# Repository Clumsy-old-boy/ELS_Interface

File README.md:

<!-- PROJECT SHIELDS -->
[![License][license-shield]][license-url][![Platform][platform-shield]][platform-url][![Toolchain][toolchain-shield]][toolchain-url][![Verified][verified-shield]][verified-url]

<!-- PROJECT LOGO -->
<br />
<div align="center">
  <h3 align="center">ELS_Interface — NUCLEO-G474RE Shield</h3>

  <p align="center">
    Carrier board for the STM32G474RE (NUCLEO-G474RE) that puts on a single
    70 × 70 mm PCB the field interface of an electronic machine controller:
    12 V → 5 V buck supply, serial display connector, 2×10 IDC field I/O with
    level shifting and opto-isolated outputs, I²C EEPROM and two debug LEDs.
    <br />
    <a href="#documentation"><strong>See the Documentation »</strong></a>
    <br />
    <br />
    <a href="#about-the-project">About</a>
    &middot;
    <a href="#getting-started">Getting Started</a>
    &middot;
    <a href="#verification">Verification</a>
    &middot;
    <a href="#production-files">Production Files</a>
  </p>
</div>

<!-- TABLE OF CONTENTS -->
<details>
  <summary>Table of Contents</summary>
  <ol>
    <li>
      <a href="#about-the-project">About The Project</a>
      <ul>
        <li><a href="#main-features">Main Features</a></li>
        <li><a href="#built-with">Built With</a></li>
      </ul>
    </li>
    <li>
      <a href="#getting-started">Getting Started</a>
      <ul>
        <li><a href="#prerequisites">Prerequisites</a></li>
        <li><a href="#installation">Installation</a></li>
      </ul>
    </li>
    <li><a href="#documentation">Documentation</a></li>
    <li><a href="#usage">Usage</a></li>
    <li><a href="#verification">Verification</a></li>
    <li><a href="#production-files">Production Files</a></li>
    <li><a href="#repository-structure">Repository Structure</a></li>
    <li><a href="#known-issues--limitations">Known Issues & Limitations</a></li>
    <li><a href="#contributing">Contributing</a></li>
    <li><a href="#license">License</a></li>
    <li><a href="#acknowledgments">Acknowledgments</a></li>
  </ol>
</details>

<!-- ABOUT THE PROJECT -->
## About The Project

**ELS_Interface** is a KiCad shield for the **NUCLEO-G474RE**
(STMicroelectronics **STM32G474RET6**, LQFP64). It plugs onto the two morpho
headers of the Nucleo board and carries the machine-side interface of an
electronic lead-screw (ELS) controller.

The board is a **2-layer design**, 70 × 70 mm, 1 oz copper, routed and
**DRC-clean** (0 active violations, 0 unconnected nets), with a fully filled
copper pour on both sides.

The 12 V field supply enters on a screw terminal, is protected and stepped
down to 5 V by a **TPS5430** buck converter; the 5 V rail of the shield can be
fed either from that buck or from the Nucleo USB supply through a **diode-OR**
(D4 / D5), so the board can be brought up on the bench without the 12 V
connected. The Nucleo itself is fed on the **E5V** pin (CN7-6) directly from
the buck, which keeps that pin inside the 4.75–5.25 V range specified by ST
(UM2505).

> [!WARNING]
> Hobbyist / educational project, **not certified**. The board works on 12 V
> and switches field signals through optocouplers, but no functional-safety
> claim is made: verify every interface against your machine before use.
> <br>
> This project was developed with the support of artificial intelligence
> tools — see [Verification](#verification).

### Main Features

| Item | Value |
|---|---|
| Board size | **70 × 70 mm**, 2 layers, 1 oz copper |
| MCU board | NUCLEO-G474RE (STM32G474RET6) via J1 (CN7) + J2 (CN10), 2×19, 2.54 mm |
| Supply input | **12 V DC** on J3 (2-pole screw terminal), protected by F1 polyfuse + TVS D1 |
| 5 V generation | **TPS5430** buck, 5 V / up to 3 A, L1 22 µH, C5 220 µF |
| Supply selection | **diode-OR D4/D5** (12 V rail vs. USB) on the shield 5 V rail |
| MCU supply | E5V (CN7-6), 5.00 V direct, jumper **JP5 = 5-6** on the Nucleo |
| Display | **J7** — 8-pin 2.00 mm (DWIN DMG10600C101), 12 V + TTL UART |
| Field I/O | **J5** — IDC 2×10, level-shifted by **TXB0104** |
| Isolated outputs | **3 × PC817** optocouplers → **J8** (5-pole screw terminal) |
| Memory | **M24M01E** 1 Mbit I²C EEPROM (IC1) |
| Debug LEDs | LED1 green on **PA0**, LED2 red on **PA1**, 0402 resistors |
| Assembly | **56 components**, JLCPCB-ready (BOM + CPL + LCSC codes) |

### Built With

* [![KiCad][kicad-shield]][kicad-url]
* [![STMicroelectronics][st-shield]][st-url]
* [Electra 6.x](https://www.layouteditor.com/) — autorouter used for the initial PCB routing

<p align="right">(<a href="#readme-top">back to top</a>)</p>

<!-- GETTING STARTED -->
## Getting Started

### Prerequisites

* **KiCad 10** (developed and verified with **10.0.6**).
* No external libraries are needed: symbols, footprints and 3D models are
  stored inside `library/` and referenced with `${KIPRJMOD}`.

### Installation

1. Clone the repository:
   ```sh
   git clone https://github.com/Clumsy-old-boy/ELS_Interface.git
   ```
2. Open `ELS_Interface.kicad_pro` with KiCad 10.
3. Check that the library tables are loaded: *Preferences → Manage Symbol
   Libraries* and *Manage Footprint Libraries* must show `ELS_Custom`,
   `User_Library`, `User_Footprints` and the `PCM_*_AKL` entries, all with
   `${KIPRJMOD}` paths.

<p align="right">(<a href="#readme-top">back to top</a>)</p>

<!-- DOCUMENTATION -->
## Documentation

| Document | File | Description |
|---|---|---|
| Usage | [`docs/USAGE.md`](docs/USAGE.md) | Supply, connectors, LEDs, Nucleo jumper JP5 |
| Configuration | [`docs/CONFIGURATION.md`](docs/CONFIGURATION.md) | Pinout, connected components, logic levels, connector map |
| Test procedure | [`docs/TEST_PROCEDURE.md`](docs/TEST_PROCEDURE.md) | Power-up, LED, opto, display and IDC tests |
| User guide (PDF) | [`docs/USAGE.pdf`](docs/USAGE.pdf) | Printable user guide, 8 pages |
| Configuration (PDF) | [`docs/CONFIGURATION.pdf`](docs/CONFIGURATION.pdf) | Printable hardware configuration, 8 pages |
| Test procedure (PDF) | [`docs/TEST_PROCEDURE.pdf`](docs/TEST_PROCEDURE.pdf) | Printable bench checklist, 11 pages |
| Schematic | [`docs/ELS_Interface_schematics.pdf`](docs/ELS_Interface_schematics.pdf) | Full schematic, single A4 sheet, with title block and revision |
| PCB layout | [`docs/pcb.pdf`](docs/pcb.pdf) | Top view with all **55** reference designators and bottom view with the two morpho sockets (J1/J2) — 2 pages |
| Interactive BOM | [`docs/ELS_Interface_ibom.html`](docs/ELS_Interface_ibom.html) | Interactive assembly drawing (iBOM), generated with InteractiveHtmlBom |
| 3D render | [`docs/ELS_Interface_board.png`](docs/ELS_Interface_board.png) | Top 3D view of the assembled board, transparent background |

<p align="right">(<a href="#readme-top">back to top</a>)</p>

<!-- USAGE -->
## Usage

Quick start:

1. Set **JP5 on the Nucleo to pins 5-6 (`E5V`)** if the board supplies the
   Nucleo from 12 V.
2. Connect **12 V** to `J3` (pin 1 = +12 V, pin 2 = GND).
3. The **LED1 (green)** and **LED2 (red)** are driven by PA0 and PA1 of the
   firmware; they are debug indicators, not power indicators.
4. The shield 5 V rail is taken from the buck when 12 V is present, or from
   USB (through D5) when the board is used on the bench.

Full details: [`docs/USAGE.md`](docs/USAGE.md).

<p align="right">(<a href="#readme-top">back to top</a>)</p>

<!-- VERIFICATION -->
## Verification

The schematic and the PCB were verified with the **`kicad-mcp-pro`** MCP
server (KiCad 10.0.6) and with **`kicad-cli`**. The checks below were run on
the exact files contained in this repository.

| Check | Tool | Result |
|---|---|---|
| **ERC** — Electrical Rules Check | `kicad-mcp-pro` / `kicad-cli` | **0 violations** |
| **DRC** — Design Rules Check incl. custom JLCPCB rules | `kicad-mcp-pro` / `kicad-cli` | **0 active violations**, **0 unconnected items** |
| **Netlist** export | `kicad-cli sch export netlist` | completed, **56 components** |
| **Schematic ↔ PCB parity** | `kicad-mcp-pro` (`validate_footprints_vs_schematic`) | **56 refs = 56 refs**, 0 missing in both directions |
| **Connectivity** | `kicad-mcp-pro` (`pcb_get_ratsnest`) | **0 unconnected nets** |
| **DFM (JLCPCB)** | measurement on the `.kicad_pcb` | 2 layers · min track 0.25 mm · via 0.40/0.80 mm · min PTH 0.30 mm · 0 silk-to-pad violations |

> [!NOTE]
> Two DRC items are **excluded in the project** on purpose and are therefore
> not counted as active violations:
> `U1` *footprint type mismatch* (the SO-PowerPAD footprint of the TPS5430 has
> thermal vias, which the checker reports as an SMD/through-hole mismatch) and
> `F1` *footprint differs from the library copy* (a locally adjusted polyfuse
> footprint, already reflected in the Gerber files).

<p align="right">(<a href="#readme-top">back to top</a>)</p>

<!-- PRODUCTION -->
## Production Files

Everything needed to order the PCB and the SMT assembly at **JLCPCB**:

| File | Content |
|---|---|
| [`production/GERBER-ELS_Interface.zip`](jlcpcb/production_files/GERBER-ELS_Interface.zip) | Gerber (9 layers) + PTH / NPTH drill files |
| [`production/BOM-ELS_Interface.csv`](jlcpcb/production_files/BOM-ELS_Interface.csv) | Bill of materials with **LCSC part numbers** (50 components) |
| [`production/CPL-ELS_Interface.csv`](jlcpcb/production_files/CPL-ELS_Interface.csv) | Component placement (designator, X, Y, rotation, layer) |

Manufacturing rules matching JLCPCB 2-layer / 1 oz capability are in
[`ELS_Interface.kicad_dru`](ELS_Interface.kicad_dru).

> [!IMPORTANT]
> The through-hole connectors (J1, J2, J3, J5, J7, J8) are **excluded from
> the BOM and CPL** on purpose: they are not assembled by JLCPCB and must be
> soldered by hand.

<p align="right">(<a href="#readme-top">back to top</a>)</p>

<!-- REPOSITORY STRUCTURE -->
## Repository Structure

```
ELS_Interface/
├── ELS_Interface.kicad_pro      KiCad project
├── ELS_Interface.kicad_sch      Schematic
├── ELS_Interface.kicad_pcb      PCB, routed and DRC-clean
├── ELS_Interface.kicad_dru      Custom DRC rules for JLCPCB (2 layers, 1 oz)
├── fp-lib-table                 Footprint library table (${KIPRJMOD})
├── sym-lib-table                Symbol library table (${KIPRJMOD})
├── library/                     Project libraries and 3D models
│   ├── ELS_Custom.kicad_sym     Project-specific symbols
│   ├── ELS_Custom.pretty/       Project-specific footprints
│   ├── User_Library.kicad_sym   Power symbols (E5V, V_5V_SHIELD)
│   ├── User_Footprints.pretty/  Extra footprints (SOIC-8)
│   ├── *_AKL.kicad_sym          Alternate KiCad Library (vendored)
│   ├── *_AKL.pretty/            Alternate KiCad Library footprints (vendored)
│   └── 3d/                      STEP models used by the board
├── docs/                        PDF schematic, PCB view, iBOM and guides
└── jlcpcb/production_files/     Gerber ZIP, BOM, CPL — ready for JLCPCB
```

<p align="right">(<a href="#readme-top">back to top</a>)</p>

<!-- KNOWN ISSUES -->
### Known Issues & Limitations

- **Nucleo jumper JP5 must be set correctly**: `5-6` (E5V) when the board
  supplies the Nucleo, `1-2` (STLK) when the Nucleo is powered from USB.
- **Through-hole connectors are not assembled** by the SMT service; the
  40-pin morpho headers (J1/J2) and J3/J5/J7/J8 must be soldered by hand.
- **I²C3 pin mapping**: the `.ioc` enables I2C3 with custom timing but does not
  assign SCL/SDA; on the board the EEPROM is wired to **PC8/PC11** — confirm
  the mapping in CubeMX before generating the firmware.
- The **firmware is not included** in this repository: it lives in a separate
  STM32CubeMX/Keil project.
- The routing scripts used during development (Electra `.do` files and the
  Specctra `.dsn`) are not distributed with the repository.

<p align="right">(<a href="#readme-top">back to top</a>)</p>

<!-- CONTRIBUTING -->
## Contributing

1. Fork the Project
2. Create your Feature Branch (`git checkout -b feature/NewFeature`)
3. Commit your Changes (`git commit -m 'Add NewFeature'`)
4. Push to the Branch (`git push origin feature/NewFeature`)
5. Open a Pull Request

<p align="right">(<a href="#readme-top">back to top</a>)</p>

<!-- LICENSE -->
## License

Distributed under the **MIT** license. See [`LICENSE`](LICENSE) for the full text.

<p align="right">(<a href="#readme-top">back to top</a>)</p>

<!-- ACKNOWLEDGMENTS -->
## Acknowledgments

* [STMicroelectronics — STM32G4 Series](https://www.st.com/en/microcontrollers-microprocessors/stm32g4-series.html)
* [NUCLEO-G474RE user manual (UM2505)](https://www.st.com/resource/en/user_manual/um2505-stm32g4-nucleo64-boards-mb1367-stmicroelectronics.pdf)
* [JLCPCB PCB capabilities](https://jlcpcb.com/capabilities/pcb-capabilities)
* [kicad-druid — JLCPCB design rules for KiCad](https://github.com/Cimos/kicad-druid)
* [Best-README-Template](https://github.com/othneildrew/Best-README-Template) — structure of this README
* This project was developed with the support of artificial intelligence tools.

<p align="right">(<a href="#readme-top">back to top</a>)</p>

<!-- MARKDOWN LINKS & IMAGES -->
[license-shield]: https://img.shields.io/badge/license-MIT-yellow.svg?style=for-the-badge
[license-url]: LICENSE
[platform-shield]: https://img.shields.io/badge/MCU-STM32G474RE-03234B?style=for-the-badge
[platform-url]: https://www.st.com/en/microcontrollers-microprocessors/stm32g474re.html
[toolchain-shield]: https://img.shields.io/badge/toolchain-KiCad%2010-1C6BB0?style=for-the-badge
[toolchain-url]: https://www.kicad.org/
[verified-shield]: https://img.shields.io/badge/ERC%200%20%7C%20DRC%200-passing-brightgreen?style=for-the-badge
[verified-url]: #verification
[kicad-shield]: https://img.shields.io/badge/KiCad-10.0.6-1C6BB0?style=for-the-badge
[kicad-url]: https://www.kicad.org/
[st-shield]: https://img.shields.io/badge/STMicroelectronics-STM32G4-03234B?style=for-the-badge
[st-url]: https://www.st.com/en/microcontrollers-microprocessors/stm32g4-series.html

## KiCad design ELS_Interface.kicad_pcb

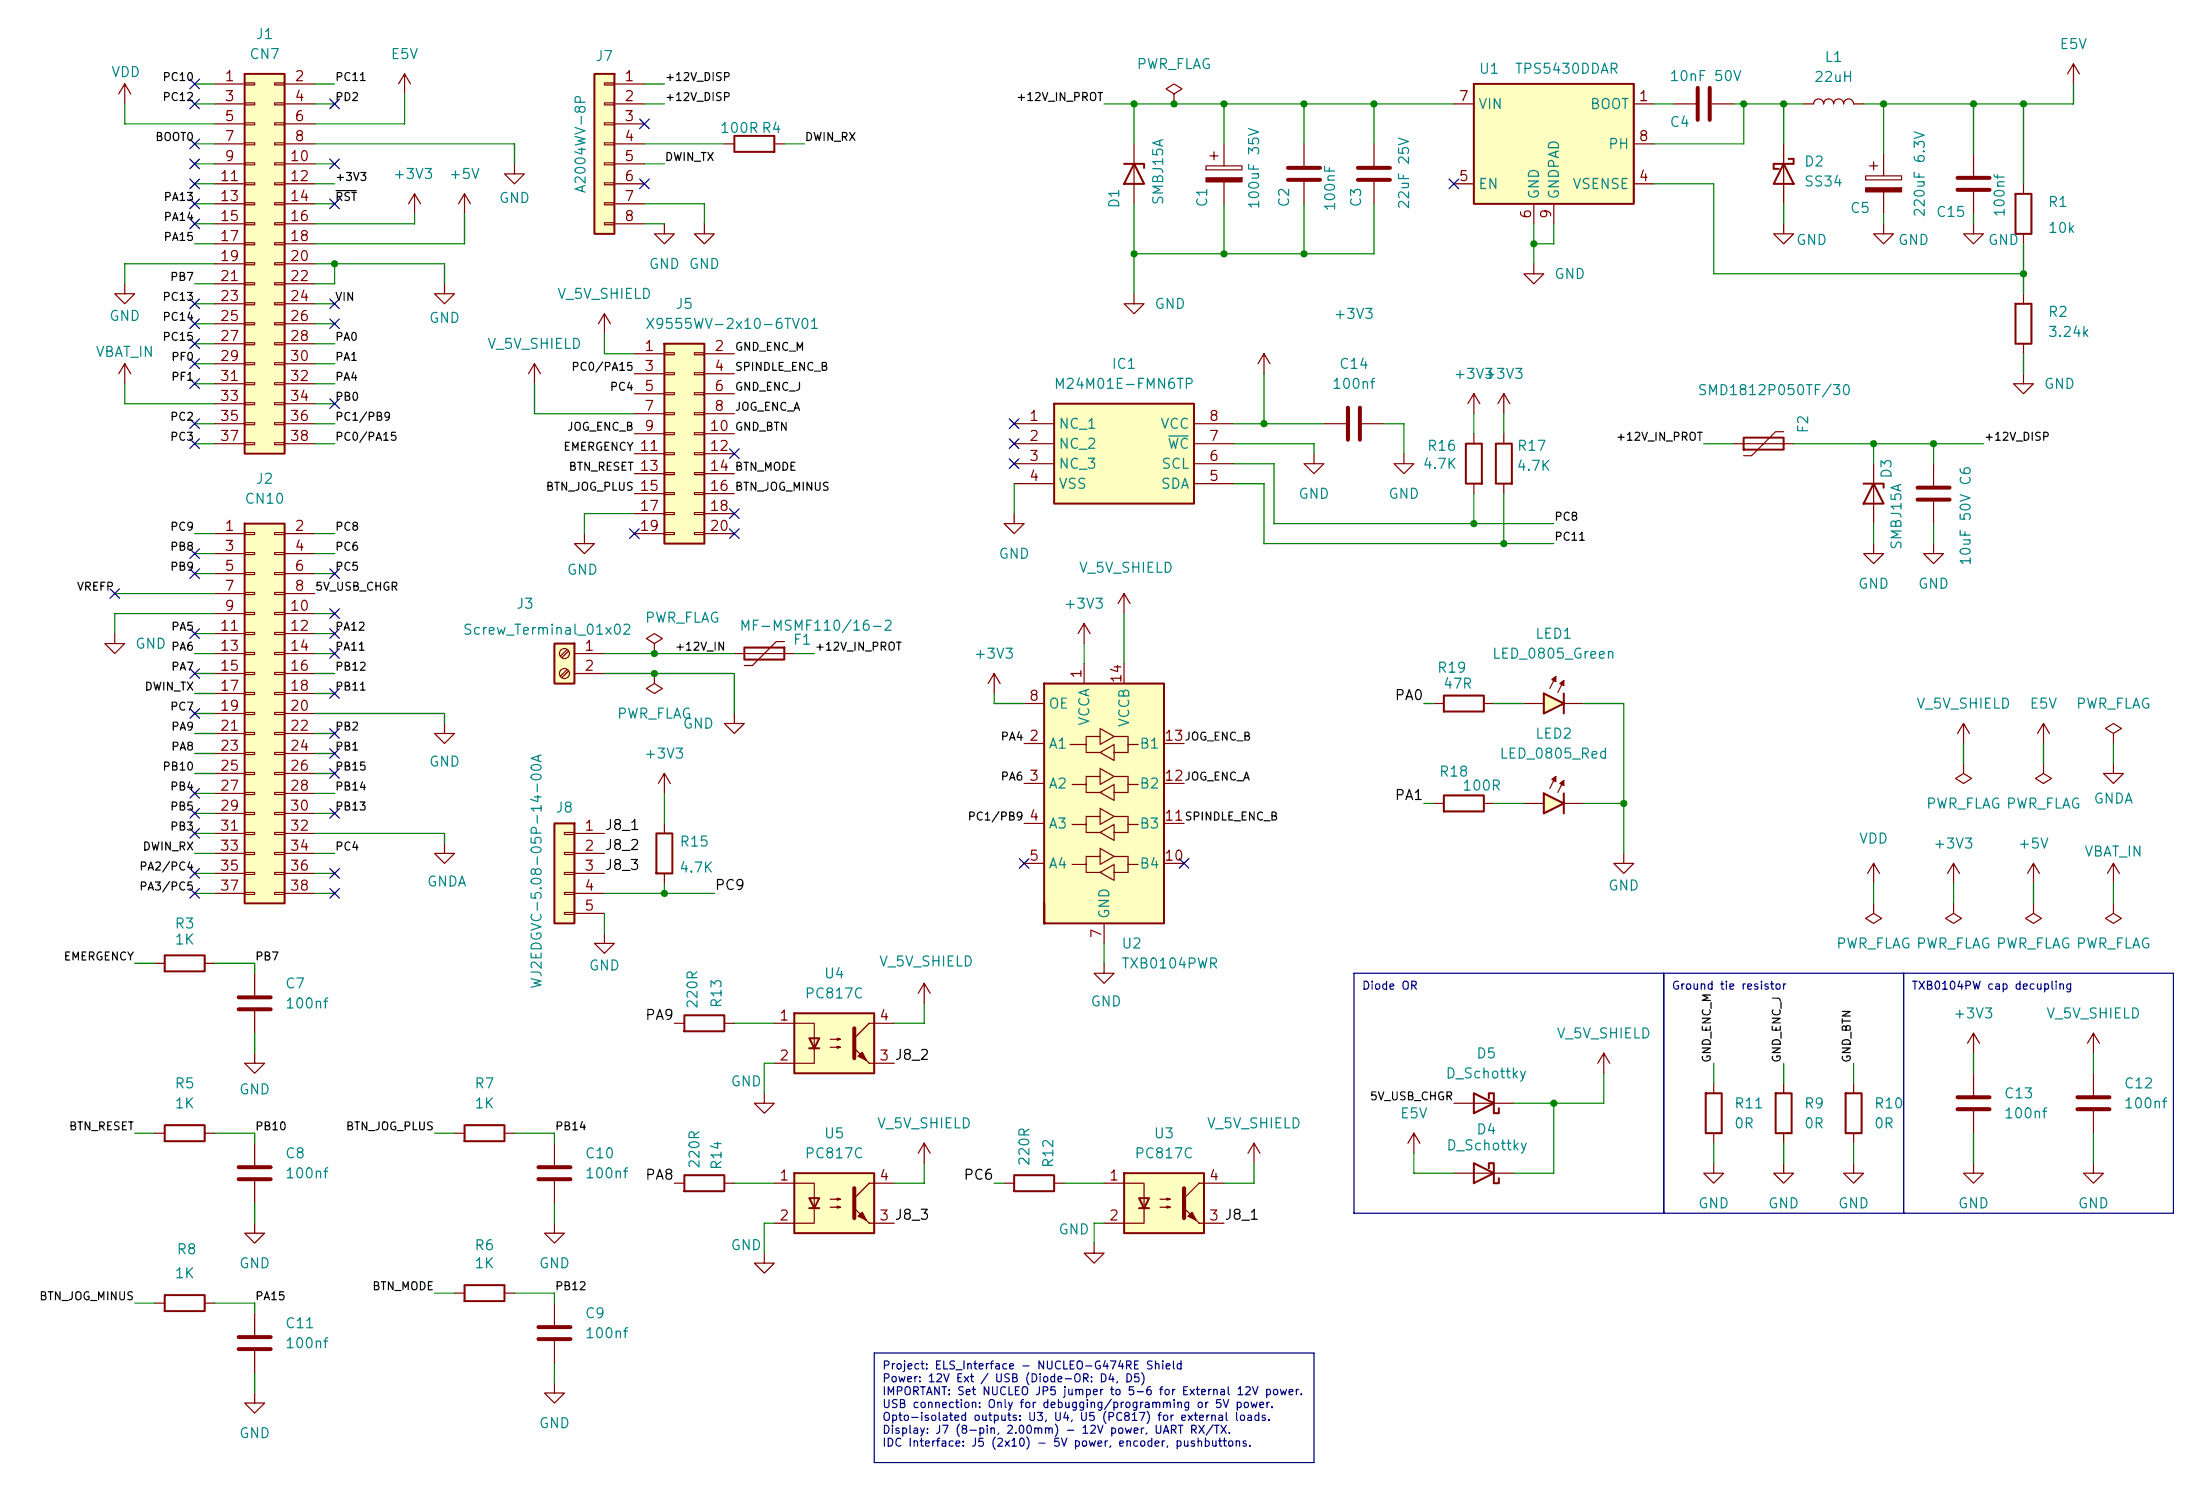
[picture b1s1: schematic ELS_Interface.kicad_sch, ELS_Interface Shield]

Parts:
C1: 100uF 35V; CP_Elec_6.3x7.7; MPN MA35V100M6X8; LCSC C46550467
C2: 100nF; C_0603_1608Metric; MPN CC0603KRX7R9BB104; LCSC C14663
C3: 22uF 25V; C_1210_3225Metric; MPN TCC1210X7R226K250MT; LCSC C49118556
C4: 10nF 50V; C_0805_2012Metric; MPN 08055C103KAT2A; LCSC C128911
C5: 220uF 6.3V; CP_EIA-3528-21_Kemet-B; MPN 6TPE220MAZB; LCSC C79111
C6: 10uF 50V; C_1206_3216Metric; MPN CL31A106KBHNNNE; LCSC C13585
C7, C8, C9, C10, C11, C12, C13, C14, C15: 100nf; C_0603_1608Metric; MPN CC0603KRX7R9BB104; LCSC C14663
D1, D3: SMBJ15A; D_SMB; MPN SMBJ15A; LCSC C188412
D2: SS34; D_SMB; MPN SS34; LCSC C908684
D4, D5: D_Schottky; D_SOD-123; LCSC C8598
F1: MF-MSMF110/16-2; Fuse_1812_4532Metric_JLCPCB; MPN MF-MSMF110/16-2; LCSC C210834
F2: SMD1812P050TF/30; Fuse_1812_4532Metric_JLCPCB; MPN SMD1812P050TF/30; LCSC C12559
IC1: M24M01E-FMN6TP; SOIC127P600X175-8N; Manufacturer_Part_Number M24M01E-FMN6TP; Mouser Part Number 511-M24M01E-FMN6TP
J1: CN7; PinSocket_2x19_P2.54mm_Vertical; MPN XDM254-2-19-Z-8.5-G0; LCSC C19268731
J2: CN10; PinSocket_2x19_P2.54mm_Vertical; MPN XDM254-2-19-Z-8.5-G0; LCSC C19268731
J3: Screw_Terminal_01x02; TerminalBlock_Phoenix_PT-1,5-2-3.5-H_1x02_P3.50mm_Horizontal; MPN DB125-3.5-2P-GN-S; LCSC C466970
J5: X9555WV-2x10-6TV01; IDC-Header_2x10_P2.54mm_Vertical; MPN X9555WV-2x10-6TV01; LCSC C2884550
J7: A2004WV-8P; CONN-TH_CNJMA2004WV-8P; MPN A2004WV-8P; LCSC C225246
J8: WJ2EDGVC-5.08-05P-14-00A; MPN WJ2EDGVC-5.08-05P-14-00A; LCSC C8423
L1: 22uH; L_Bourns-SRN8040_8x8.15mm; MPN FNR8065S220MT; LCSC C168163
LED1: LED_0805_Green; LED_0805_2012Metric; LCSC C2297
LED2: LED_0805_Red; LED_0805_2012Metric; LCSC C84256
R1: 10k; R_0402_1005Metric_Fixed; MPN 0402WGF1002TCE; LCSC C25744
R2: 3.24k; R_0402_1005Metric_Fixed; MPN CRCW04023K24FKED; LCSC C3972407
R3, R5, R6, R7, R8: 1K; R_0402_1005Metric_Fixed; MPN 0402WGF1001TCE; LCSC C11702
R4, R18: 100R; R_0402_1005Metric_Fixed; MPN 0402WGF1000TCE; LCSC C25076
R9, R10, R11: 0R; R_0603_1608Metric; MPN 0603WAF0000T5E; LCSC C21189
R12, R13, R14: 220R; R_0402_1005Metric_Fixed; MPN 0402WGF2200TCE; LCSC C25091
R15, R16, R17: 4.7K; R_0402_1005Metric_Fixed; MPN 0402WGF4701TCE; LCSC C25900
R19: 47R; R_0402_1005Metric_Fixed; MPN 0402WGF1000TCE; LCSC C25118
U1: TPS5430DDAR; TI_SO-PowerPAD-8_ThermalVias_JLCPCB; MPN TPS5430DDAR; LCSC C9864
U2: TXB0104PWR; TSSOP-14_4.4x5mm_P0.65mm; MPN TXB0104PWR; LCSC C60708
U3, U4, U5: PC817C; OPTO-SMD-4_L4.6-W6.5-P2.54-LS10.3-TL; MPN PC817C; LCSC C3025164

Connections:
+3V3: C13.1, C14.1, IC1.8 (VCC), J1.12, J1.16, R15.2, R16.2, R17.2, U2.1 (VCCA), U2.8 (OE)
+5V: J1.18
/5V_USB_CHGR: D5.2 (A), J2.8
/+12V_DISP: C6.1, D3.1 (K), F2.2, J7.1, J7.2
/+12V_IN: F1.2, J3.1
/+12V_IN_PROT: C1.1, C2.1, C3.1, D1.1 (K), F1.1, F2.1, U1.7 (VIN)
/BOOT0: J1.7
/BTN_JOG_MINUS: J5.16, R8.1
/BTN_JOG_PLUS: J5.15, R7.1
/BTN_MODE: J5.14, R6.1
/BTN_RESET: J5.13, R5.1
/DWIN_RX: J2.33, R4.1
/DWIN_TX: J2.17, J7.5
/EMERGENCY: J5.11, R3.1
/GND_BTN: J5.10, R10.1
/GND_ENC_J: J5.6, R9.1
/GND_ENC_M: J5.2, R11.1
/J8_1: J8.1, U3.3
/J8_2: J8.2, U4.3
/J8_3: J8.3, U5.3
/JOG_ENC_A: J5.8, U2.12 (B2)
/JOG_ENC_B: J5.9, U2.13 (B1)
/PA0: J1.28, R19.1
/PA1: J1.30, R18.1
/PA2/PC4: J2.35
/PA3/PC5: J2.37
/PA4: J1.32, U2.2 (A1)
/PA5: J2.11
/PA6: J2.13, U2.3 (A2)
/PA7: J2.15
/PA8: J2.23, R14.1
/PA9: J2.21, R13.1
/PA11: J2.14
/PA12: J2.12
/PA13: J1.13
/PA14: J1.15
/PA15: C11.1, J1.17, R8.2
/PB0: J1.34
/PB1: J2.24
/PB2: J2.22
/PB3: J2.31
/PB4: J2.27
/PB5: J2.29
/PB7: C7.1, J1.21, R3.2
/PB8: J2.3
/PB9: J2.5
/PB10: C8.1, J2.25, R5.2
/PB11: J2.18
/PB12: C9.1, J2.16, R6.2
/PB13: J2.30
/PB14: C10.1, J2.28, R7.2
/PB15: J2.26
/PC0/PA15: J1.38, J5.3
/PC1/PB9: J1.36, U2.4 (A3)
/PC2: J1.35
/PC3: J1.37
/PC4: J2.34, J5.5
/PC5: J2.6
/PC6: J2.4, R12.1
/PC7: J2.19
/PC8: IC1.6 (SCL), J2.2, R16.1
/PC9: J2.1, J8.4, R15.1
/PC10: J1.1
/PC11: IC1.5 (SDA), J1.2, R17.1
/PC12: J1.3
/PC13: J1.23
/PC14: J1.25
/PC15: J1.27
/PD2: J1.4
/PF0: J1.29
/PF1: J1.31
/SPINDLE_ENC_B: J5.4, U2.11 (B3)
/VIN: J1.24
/VREFP: J2.7
/~RST: J1.14
E5V: C5.1, C15.1, D4.2 (A), J1.6, L1.2, R1.1
GND: C1.2, C2.2, C3.2, C5.2, C6.2, C7.2, C8.2, C9.2, C10.2, C11.2, C12.2, C13.2, C14.2, C15.2, D1.2 (A), D2.2 (A), D3.2 (A), IC1.4 (VSS), IC1.7 (~WC), J1.8, J1.19, J1.20, J1.22, J2.9, J2.20, J3.2, J5.17, J7.7, J7.8, J8.5, LED1.1 (K), LED2.1 (K), R2.2, R9.2, R10.2, R11.2, U1.6 (GND), U1.9 (GNDPAD), U2.7 (GND), U3.2, U4.2, U5.2
GNDA: J2.32
unnamed: C4.2, D2.1 (K), L1.1, U1.8 (PH)
unnamed: J7.4, R4.2
unnamed: LED1.2 (A), R19.2
unnamed: LED2.2 (A), R18.2
unnamed: R12.2, U3.1
unnamed: R13.2, U4.1
unnamed: R14.2, U5.1
unnamed: C4.1, U1.1 (BOOT)
unnamed: R1.2, R2.1, U1.4 (VSENSE)
VBAT_IN: J1.33
VDD: J1.5
V_5V_SHIELD: C12.1, D4.1 (K), D5.1 (K), J5.1, J5.7, U2.14 (VCCB), U3.4, U4.4, U5.4

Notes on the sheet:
Project: ELS_Interface - NUCLEO-G474RE Shield Power: 12V Ext / USB (Diode-OR: D4, D5) IMPORTANT: Set NUCLEO JP5 jumper to 5-6 for External 12V power. USB connection: Only for debugging/programming or 5V power. Opto-isolated outputs: U3, U4, U5 (PC817) for external loads. Display: J7 (8-pin, 2.00mm)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
Diode OR
TXB0104PW cap decupling
Ground tie resistor

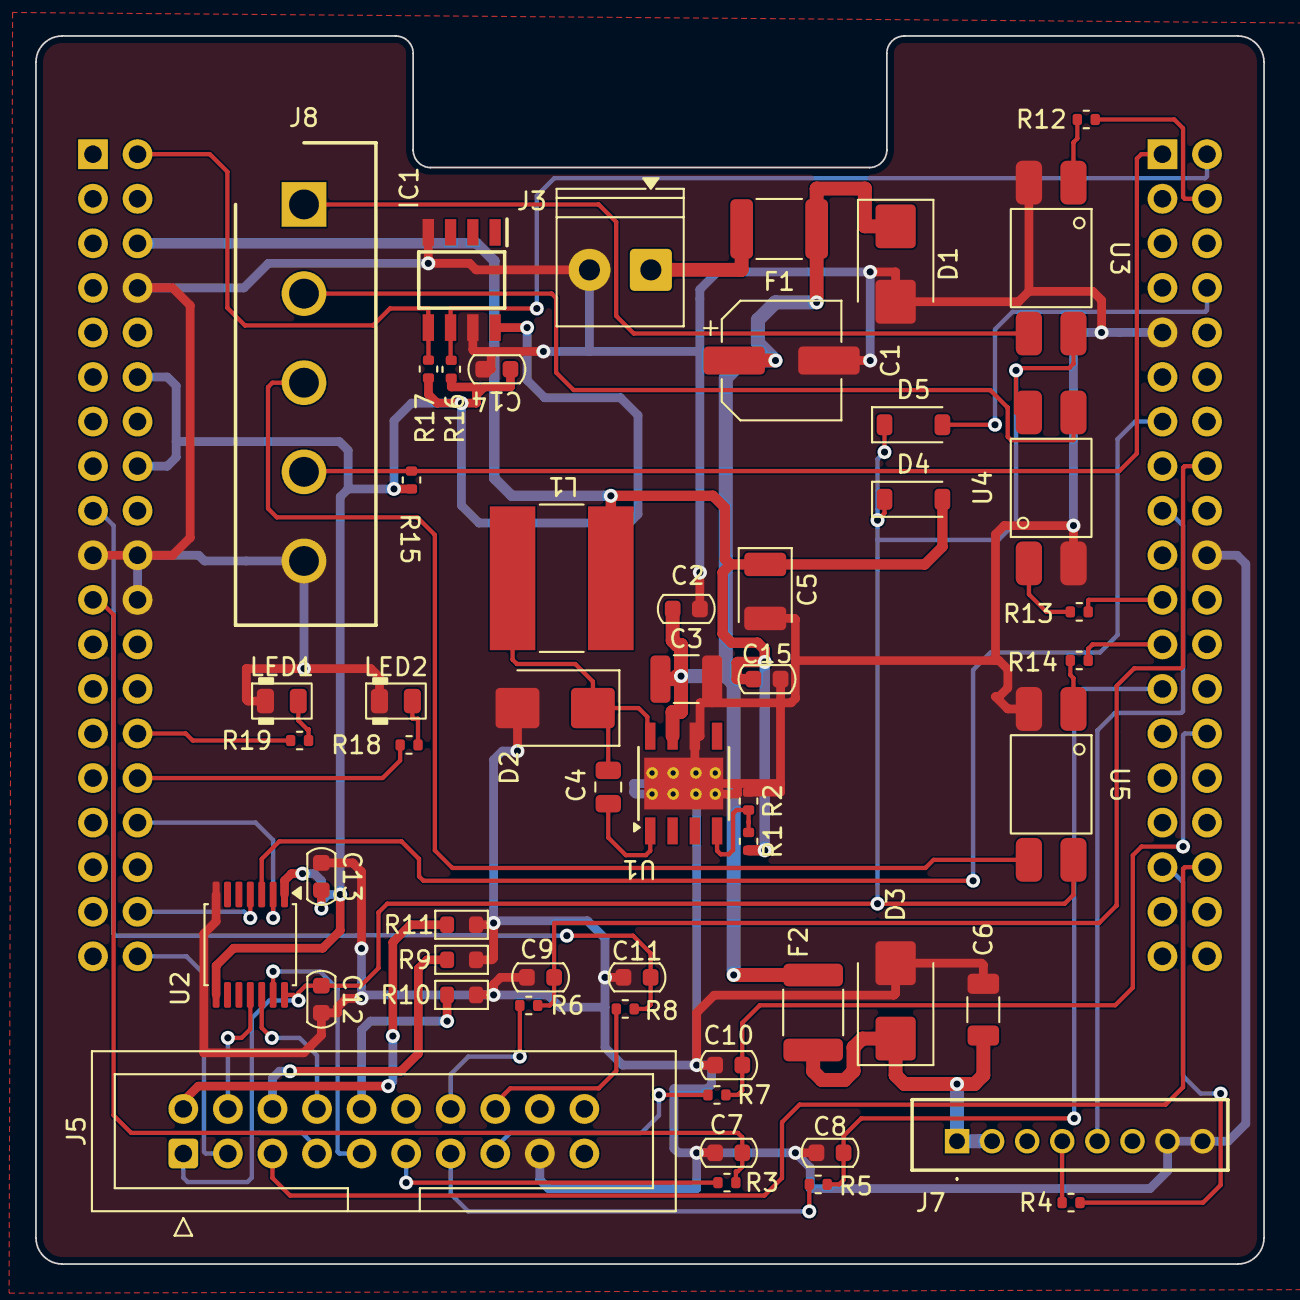
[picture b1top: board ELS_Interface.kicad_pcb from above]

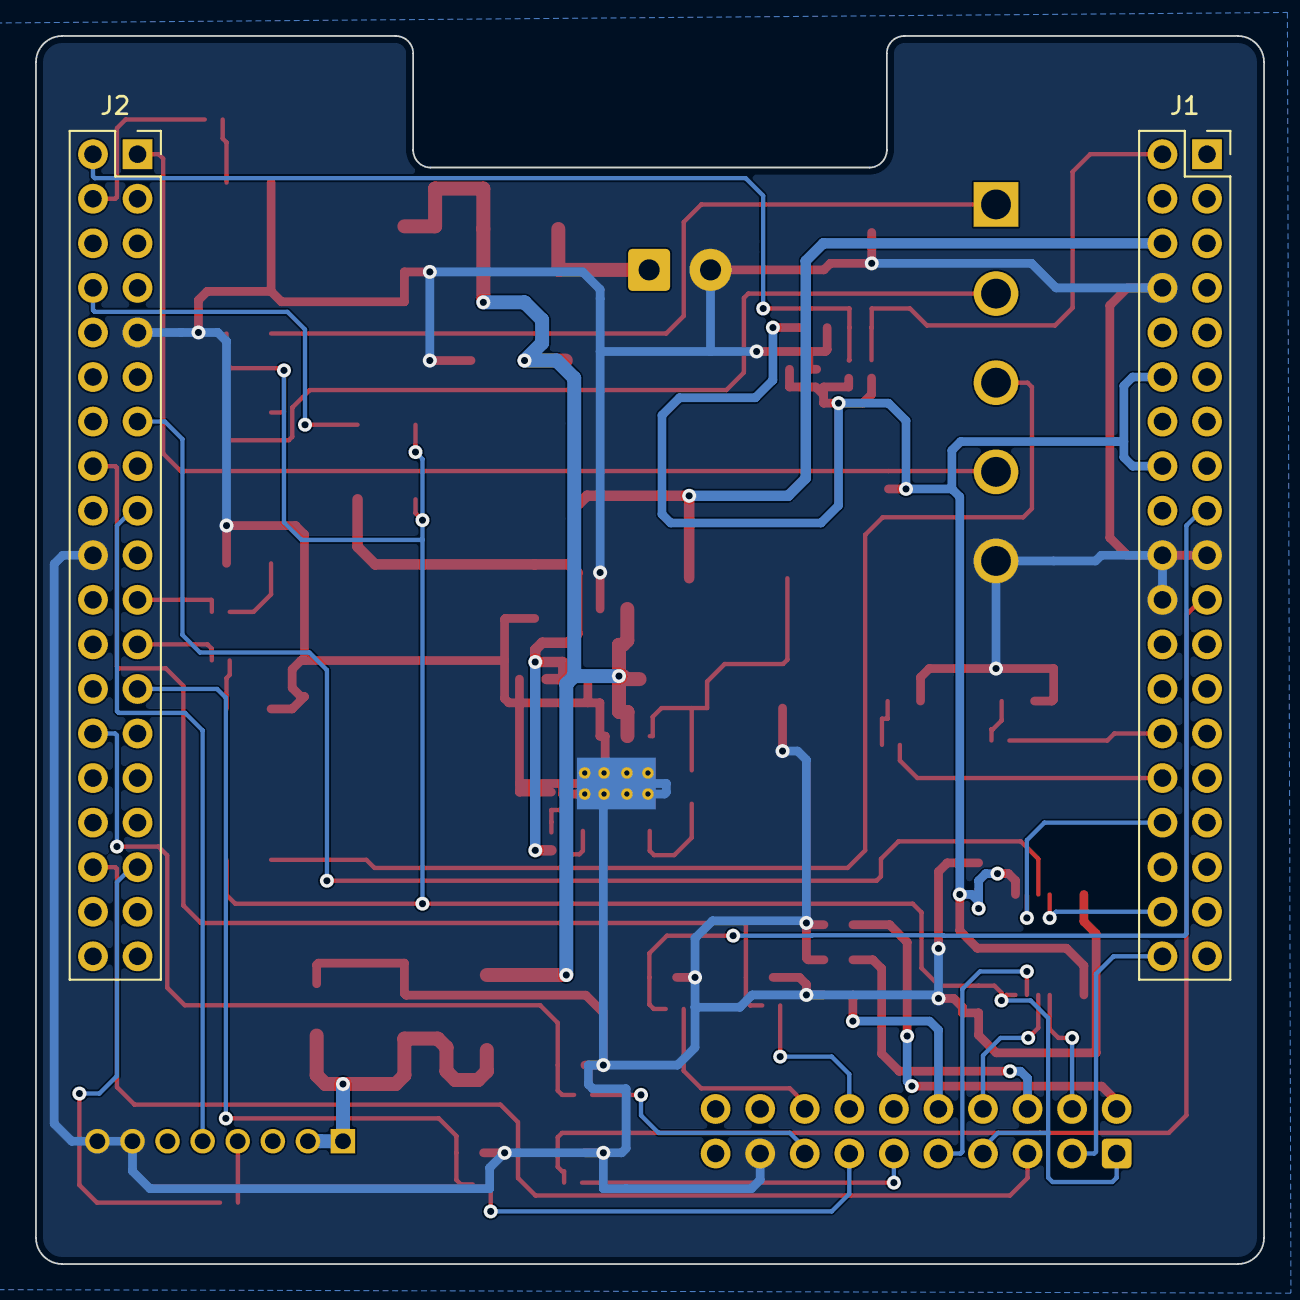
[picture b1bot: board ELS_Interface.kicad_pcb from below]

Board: 2 copper layers, 70.0 x 70.0 mm, 56 parts (2 on the bottom side), 51 nets.

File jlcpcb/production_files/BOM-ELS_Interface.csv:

Comment,Designator,Footprint,LCSC,Quantity
0R,"R10,R11,R9",R_0603_1608Metric,C21189,3
100R,"R18,R4",R_0402_1005Metric_Fixed,C25076,2
100nF,C2,C_0603_1608Metric,C14663,1
100nf,"C10,C11,C12,C13,C14,C15,C7,C8,C9",C_0603_1608Metric,C14663,9
100uF 35V,C1,CP_Elec_6.3x7.7,C46550467,1
10k,R1,R_0402_1005Metric_Fixed,C25744,1
10nF 50V,C4,C_0805_2012Metric,C128911,1
10uF 50V,C6,C_1206_3216Metric,C13585,1
1K,"R3,R5,R6,R7,R8",R_0402_1005Metric_Fixed,C11702,5
220R,"R12,R13,R14",R_0402_1005Metric_Fixed,C25091,3
220uF 6.3V,C5,CP_EIA-3528-21_Kemet-B,C79111,1
22uF 25V,C3,C_1210_3225Metric,C49118556,1
22uH,L1,L_Bourns-SRN8040_8x8.15mm,C168163,1
3.24k,R2,R_0402_1005Metric_Fixed,C3972407,1
4.7K,"R15,R16,R17",R_0402_1005Metric_Fixed,C25900,3
47R,R19,R_0402_1005Metric_Fixed,C25118,1
D_Schottky,"D4,D5",D_SOD-123,C8598,2
LED_0805_Green,LED1,LED_0805_2012Metric,C2297,1
LED_0805_Red,LED2,LED_0805_2012Metric,C84256,1
M24M01E-FMN6TP,IC1,SOIC127P600X175-8N,C19654255,1
MF-MSMF110/16-2,F1,Fuse_1812_4532Metric_JLCPCB,C210834,1
PC817C,"U3,U4,U5",OPTO-SMD-4_L4.6-W6.5-P2.54-LS10.3-TL,C3025164,3
SMBJ15A,"D1,D3",D_SMB,C188412,2
SMD1812P050TF/30,F2,Fuse_1812_4532Metric_JLCPCB,C12559,1
SS34,D2,D_SMB,C908684,1
TPS5430DDAR,U1,TI_SO-PowerPAD-8_ThermalVias_JLCPCB,C9864,1
TXB0104PWR,U2,TSSOP-14_4.4x5mm_P0.65mm,C60708,1
